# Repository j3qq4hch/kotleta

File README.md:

# kotleta
[3d view](https://a360.co/2SrLnso)

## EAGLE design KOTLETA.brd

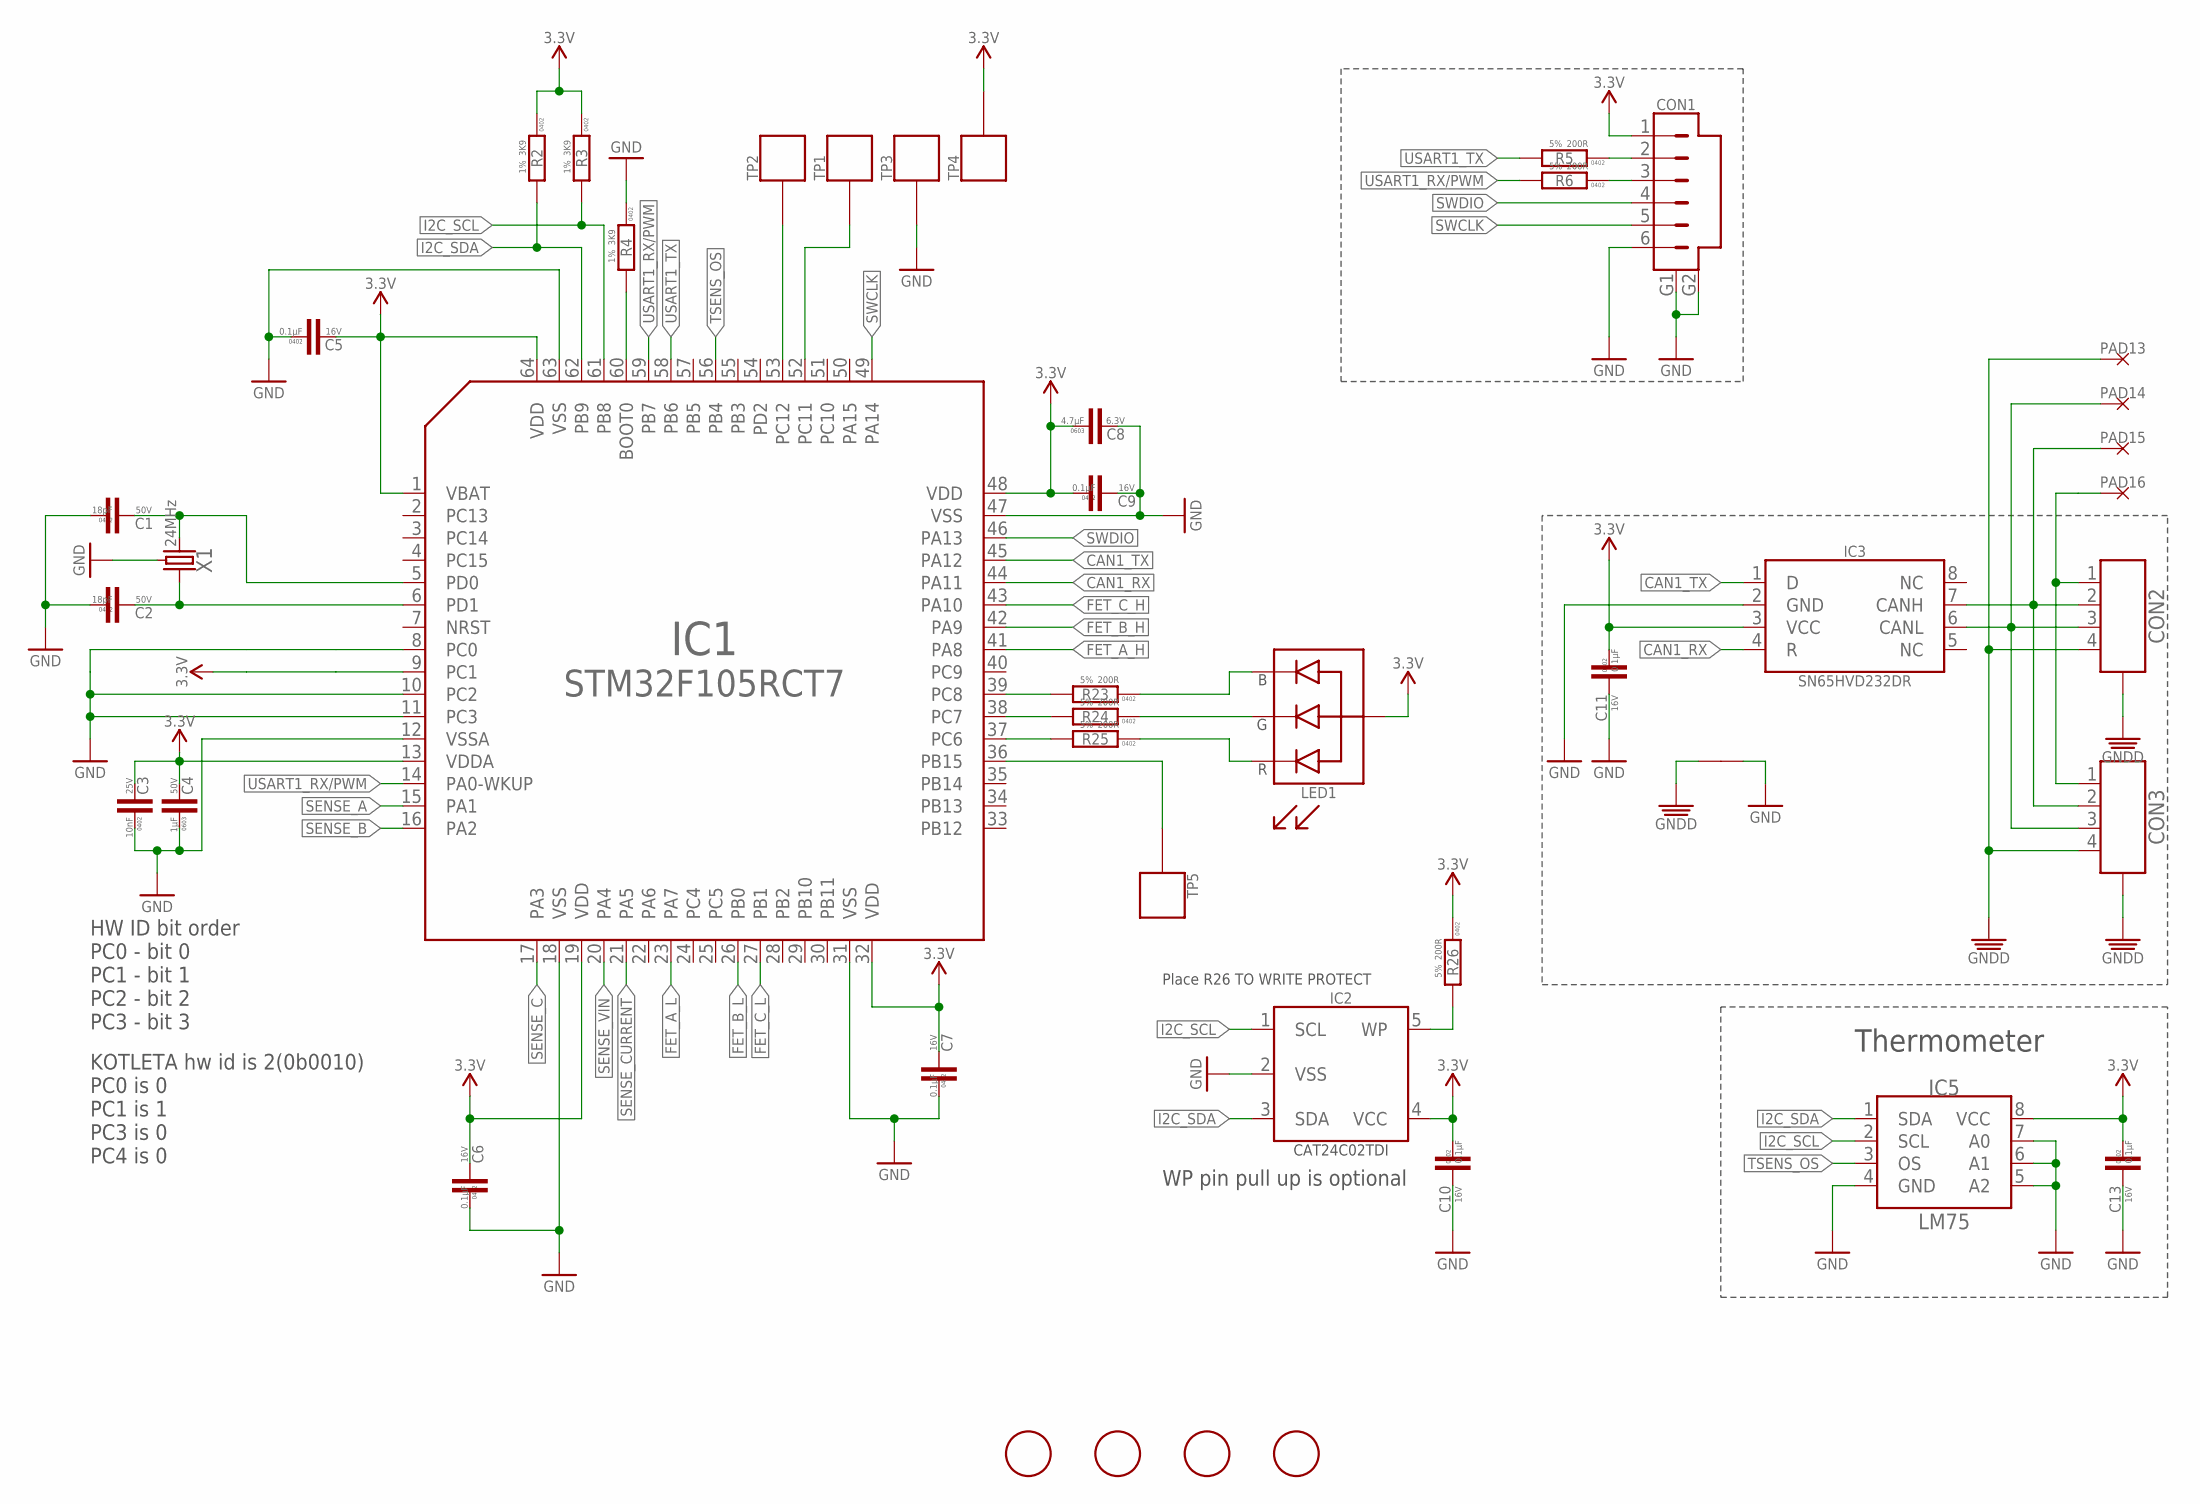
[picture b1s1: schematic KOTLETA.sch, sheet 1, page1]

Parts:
C1, C2: 18pF; C0402
C3: 10nF; C0402
C4: 1µF; C0603
C5, C6, C7, C9, C10, C11, C13: 0.1µF; C0402
C8: 4.7µF; C0603
CON1: CON-6P; SM06B; PARTNO SM06B-SRSS-TB
CON2, CON3: CON-4P-JST_GH-RA; JST_GH-4P-RA
FD1, FD2, FD3, FD4: FIDUCIALMOUNT; FIDUCIA-MOUNT
IC1: STM32F105RCT6; TQFP64; DIGIKEY# 497-11547-ND
IC2: CAT24C02; SOT23-5L
IC3: SN65HVD232D; SOIC8
IC5: LM75BD-TSSOP8; TSSOP8
LED1: LTST-C19HE1WT; LITE_ON_RGB_LED
PAD13, PAD14, PAD15, PAD16: PAD-HOLE-0.6; HOLE_0.6
R2, R3, R4: 3K9; R0402
R5, R6, R23, R24, R25, R26: 200R; R0402; PARTNO RC0402FR-07240RL
TP1, TP2, TP3, TP4, TP5: PAD.05; PAD.05X.05; PARTNO *
U$2: CONNECTION
X1: 24MHz; OSCILLATOR-3.2X2.5-4P; DIGIKEY# 1253-1198-1-ND

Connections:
BOOT0: IC1.60 (BOOT0), R4.2
CAN1_RX: IC1.44 (PA11), IC3.4 (R)
CAN1_TX: IC1.45 (PA12), IC3.1 (D)
FET_A_H: IC1.41 (PA8); also elsewhere on the board
FET_A_L: IC1.23 (PA7); also elsewhere on the board
FET_B_H: IC1.42 (PA9); also elsewhere on the board
FET_B_L: IC1.26 (PB0); also elsewhere on the board
FET_C_H: IC1.43 (PA10); also elsewhere on the board
FET_C_L: IC1.27 (PB1); also elsewhere on the board
GND: C1.1, C2.1, C3.1, C4.P$1 (1), C5.1, C6.1, C7.1, C8.P$2 (2), C9.2, C10.2, C11.2, C13.2, CON1.6, CON1.G1, CON1.G2, IC1.8 (PC0), IC1.10 (PC2), IC1.11 (PC3), IC1.12 (VSSA), IC1.18 (VSS), IC1.31 (VSS), IC1.47 (VSS), IC1.63 (VSS), IC2.2 (VSS), IC3.2 (GND), IC5.4 (GND), IC5.5 (A2), IC5.6 (A1), IC5.7 (A0), R4.1, TP3.P$1, U$2.P$2, X1.2 (GND), X1.4 (GND); also elsewhere on the board
GNDD: CON2.4, CON2.M$0 (GND), CON2.M$1 (GND), CON3.4, CON3.M$0 (GND), CON3.M$1 (GND), PAD13.P$1, U$2.P$1
I2C_SCL: IC1.61 (PB8), IC2.1 (SCL), IC5.2 (SCL), R3.2
I2C_SDA: IC1.62 (PB9), IC2.3 (SDA), IC5.1 (SDA), R2.2
unnamed: CON1.2, R5.1
unnamed: CON1.3, R6.1
unnamed: IC1.37 (PC6), R25.2
unnamed: LED1.B, R23.1
unnamed: LED1.R, R25.1
unnamed: IC2.5 (WP), R26.2
unnamed: IC1.38 (PC7), R24.2
unnamed: C1.2, IC1.5 (PD0), X1.3 (2)
unnamed: IC1.39 (PC8), R23.2
unnamed: C2.2, IC1.6 (PD1), X1.1
unnamed: CON2.1, CON3.1, PAD16.P$1
unnamed: CON2.2, CON3.2, IC3.7 (CANH), PAD15.P$1
unnamed: CON2.3, CON3.3, IC3.6 (CANL), PAD14.P$1
unnamed: LED1.G, R24.1
unnamed: IC1.53 (PC12), TP2.P$1
unnamed: IC1.36 (PB15), TP5.P$1
unnamed: IC1.52 (PC11), TP1.P$1
SENSE_A: IC1.15 (PA1); also elsewhere on the board
SENSE_B: IC1.16 (PA2); also elsewhere on the board
SENSE_C: IC1.17 (PA3); also elsewhere on the board
SENSE_CURRENT: IC1.21 (PA5); also elsewhere on the board
SENSE_VIN: IC1.20 (PA4); also elsewhere on the board
SWCLK: CON1.5, IC1.49 (PA14)
SWDIO: CON1.4, IC1.46 (PA13)
TSENS_OS: IC1.56 (PB4), IC5.3 (OS)
USART1_RX/PWM: IC1.14 (PA0-WKUP), IC1.59 (PB7), R6.2
USART1_TX: IC1.58 (PB6), R5.2
VDD_3V3: C3.2, C4.P$2 (2), C5.2, C6.2, C7.2, C8.P$1 (1), C9.1, C10.1, C11.1, C13.1, CON1.1, IC1.1 (VBAT), IC1.9 (PC1), IC1.13 (VDDA), IC1.19 (VDD), IC1.32 (VDD), IC1.48 (VDD), IC1.64 (VDD), IC2.4 (VCC), IC3.3 (VCC), IC5.8 (VCC), LED1.+ (A), R2.1, R3.1, R26.1, TP4.P$1; also elsewhere on the board

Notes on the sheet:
Thermometer
Place R26 TO WRITE PROTECT
WP pin pull up is optional
HW ID bit order PC0 - bit 0 PC1 - bit 1 PC2 - bit 2 PC3 - bit 3
KOTLETA hw id is 2(0b0010) PC0 is 0 PC1 is 1 PC3 is 0 PC4 is 0

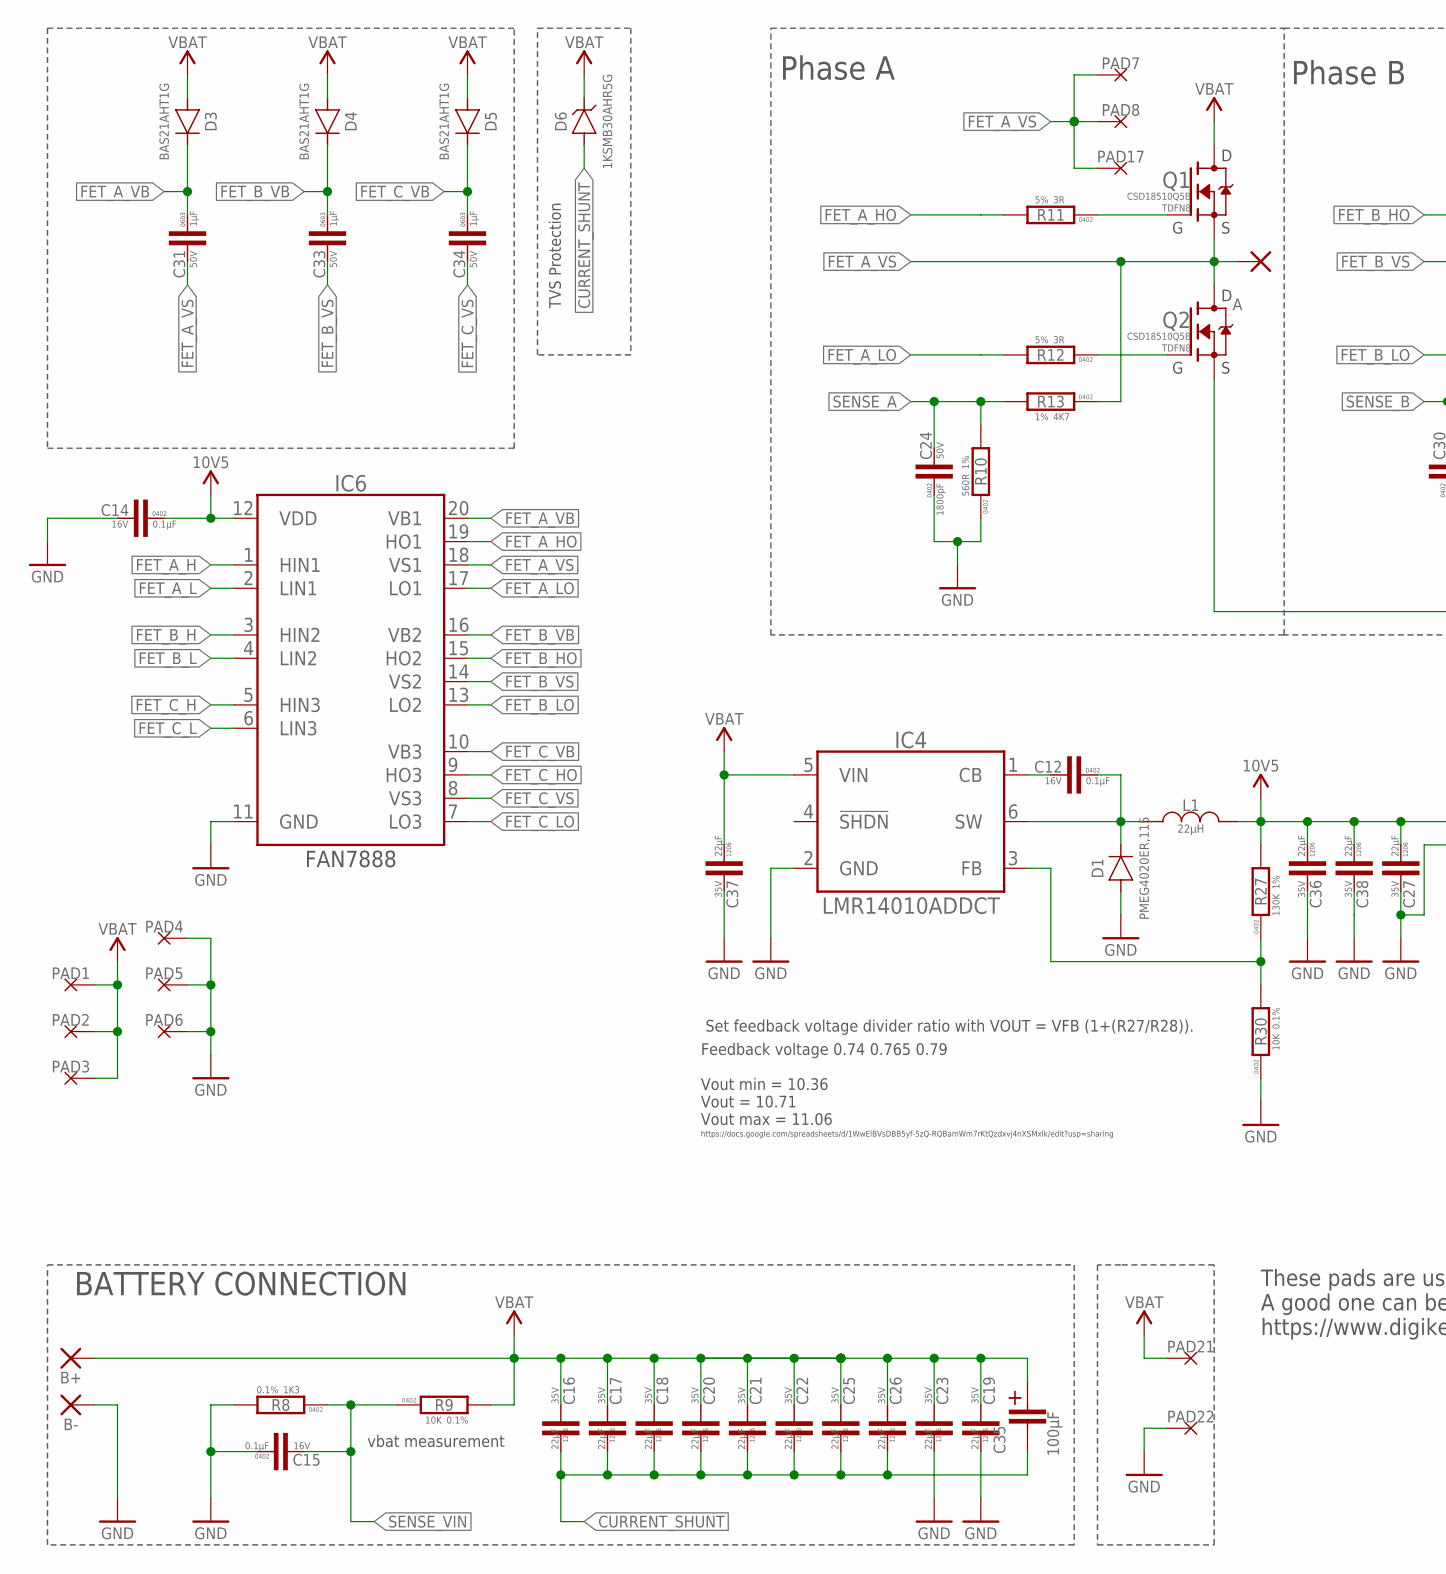
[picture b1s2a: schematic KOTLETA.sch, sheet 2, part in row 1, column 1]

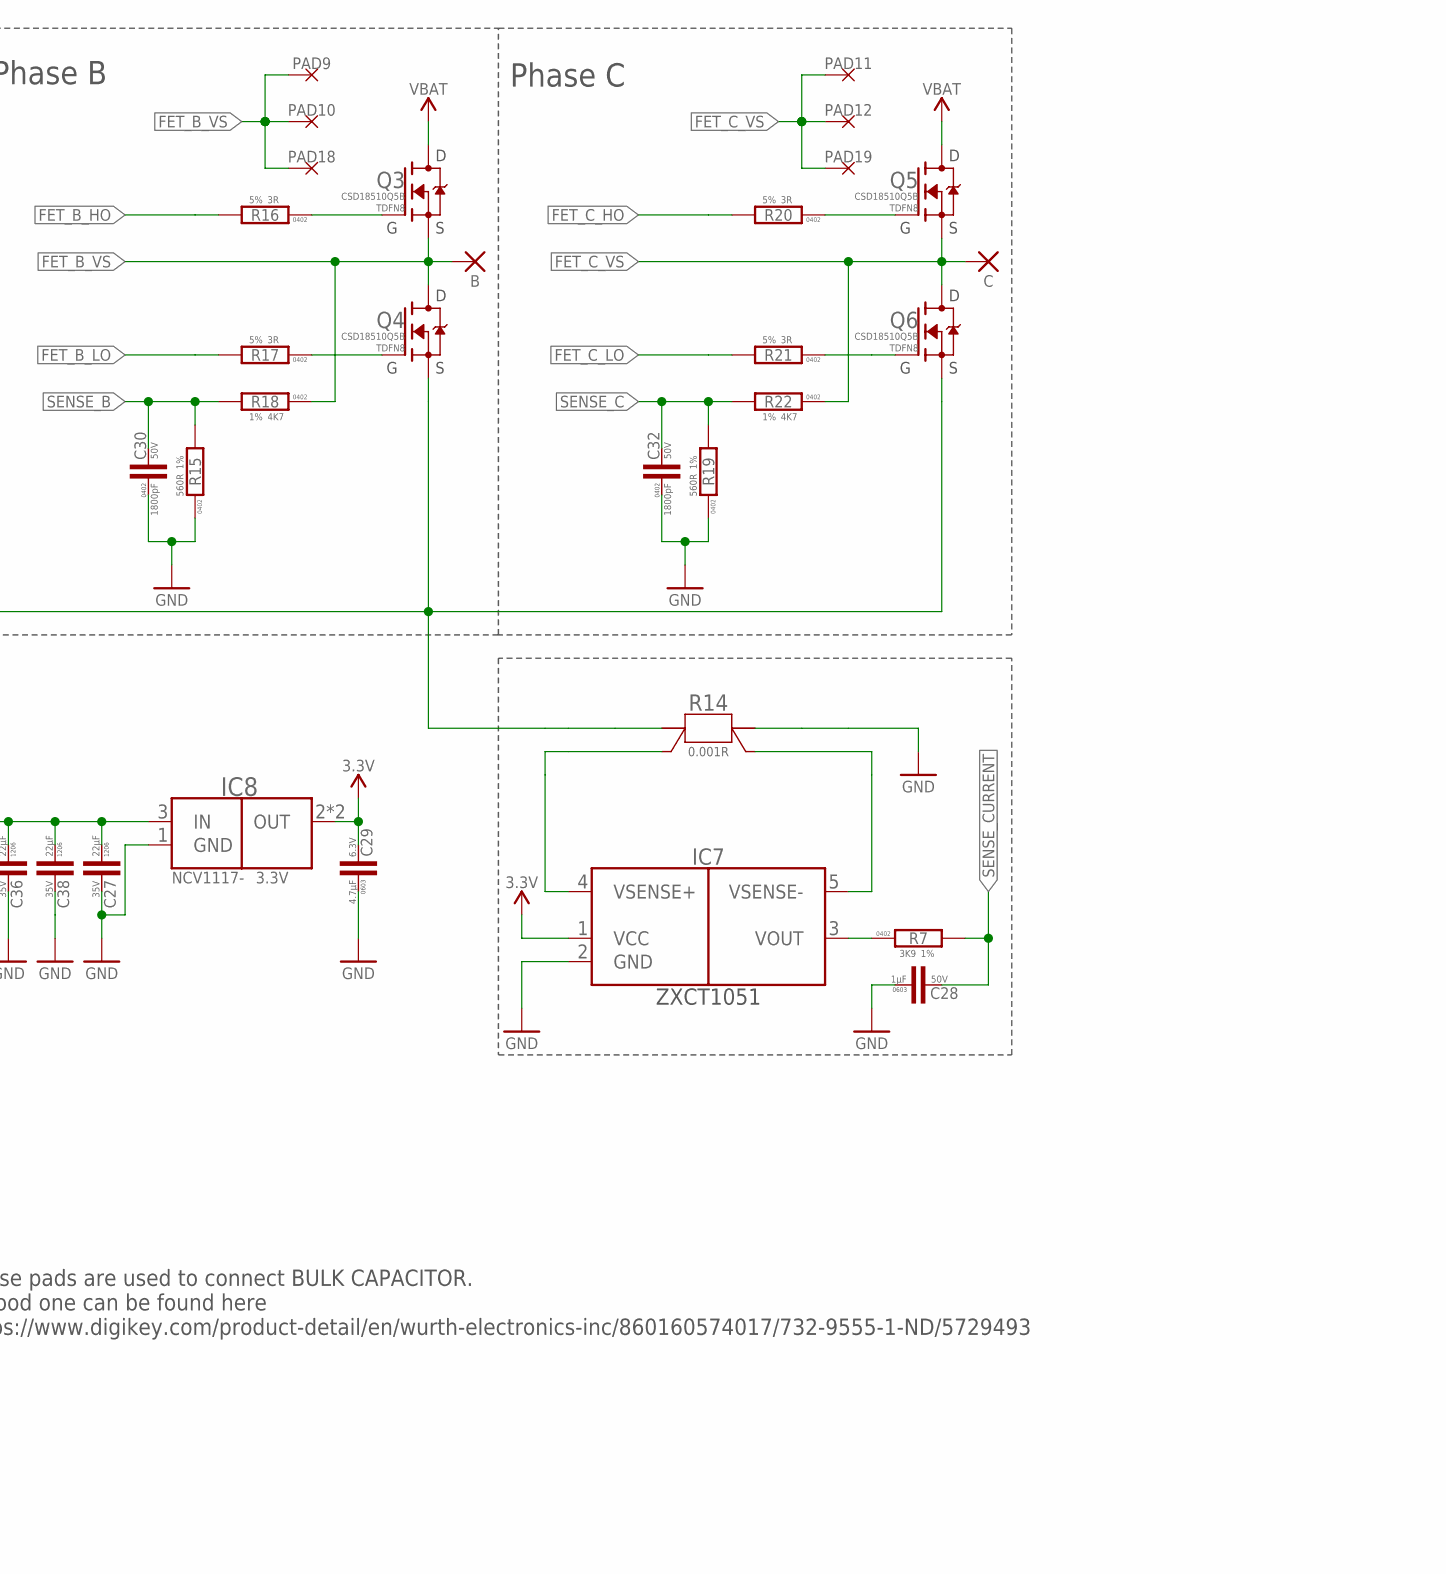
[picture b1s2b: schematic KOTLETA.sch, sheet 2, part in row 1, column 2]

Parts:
A: WIREPADSMD5-2,5; 5-2,5
B: WIREPADSMD5-2,5; 5-2,5
B+: WIREPADSMD5-2,5; 5-2,5
B-: WIREPADSMD5-2,5; 5-2,5
C: WIREPADSMD5-2,5; 5-2,5
C12, C14, C15: 0.1µF; C0402
C16, C17, C18, C19, C20, C21, C22, C23, C25, C26, C27, C36, C37, C38: 22µF; C1206
C24, C30, C32: 1800pF; C0402
C28, C31, C33, C34: 1µF; C0603
C29: 4.7µF; C0603
C35: 100µF; 3024
D1: PMEG4020; SOD123W
D3, D4, D5: BAS21AHT1G; SOD323
D6: 1KSMB30AHR5G; DO-214AA(SMB)
IC4: LMR14010ADDCT; SOT23-6
IC6: FAN7888; SOIC20; PARTNO FAN7888MX
IC7: ZXCT1051; SOT23-5L
IC8: 3.3V; SOT-223
L1: 22µH; SRN5040
PAD1, PAD2, PAD3, PAD4, PAD5, PAD6, PAD7, PAD8, PAD9, PAD10, PAD11, PAD12, PAD17, PAD18, PAD19: PAD-HOLE-0.6; HOLE_0.6
PAD21, PAD22: PAD-HOLE-0.8; HOLE_0.8
Q1, Q2, Q3, Q4, Q5, Q6: CSD18510Q5B; PG-TDSON-8
R7: 3K9; R0402
R8: 1K3; R0402
R9, R30: 10K; R0402
R10, R15, R19: 560R; R0402
R11, R12, R16, R17, R20, R21: 3R; R0402
R13, R18, R22: 4K7; R0402
R14: 0.001R; R2010-KELVIN
R27: 130K; R0402; DIGIKEY# YAG2969CT-ND

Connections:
BLABLA: IC7.3 (VOUT), R7.1
CURRENT_SHUNT: C16.P$1 (1), C17.P$1 (1), C18.P$1 (1), C20.P$1 (1), C21.P$1 (1), C22.P$1 (1), C25.P$1 (1), C26.P$1 (1), C35.-, D6.A, Q2.1S (S), Q2.2S (S), Q2.3S (S), Q4.1S (S), Q4.2S (S), Q4.3S (S), Q6.1S (S), Q6.2S (S), Q6.3S (S), R14.1, R14.11 (1)
FET_A_H: IC6.1 (HIN1); also elsewhere on the board
FET_A_HO: IC6.19 (HO1), R11.2
FET_A_L: IC6.2 (LIN1); also elsewhere on the board
FET_A_LO: IC6.17 (LO1), R12.2
FET_A_VB: C31.P$1 (1), D3.C, IC6.20 (VB1)
FET_A_VS: A.1, C31.P$2 (2), IC6.18 (VS1), PAD7.P$1, PAD8.P$1, PAD17.P$1, Q1.1S (S), Q1.2S (S), Q1.3S (S), Q2.5D (D), Q2.6D (D), Q2.7D (D), Q2.8D (D), Q2.PAD_D (D), R13.1
FET_B_H: IC6.3 (HIN2); also elsewhere on the board
FET_B_HO: IC6.15 (HO2), R16.2
FET_B_L: IC6.4 (LIN2); also elsewhere on the board
FET_B_LO: IC6.13 (LO2), R17.2
FET_B_VB: C33.P$1 (1), D4.C, IC6.16 (VB2)
FET_B_VS: B.1, C33.P$2 (2), IC6.14 (VS2), PAD9.P$1, PAD10.P$1, PAD18.P$1, Q3.1S (S), Q3.2S (S), Q3.3S (S), Q4.5D (D), Q4.6D (D), Q4.7D (D), Q4.8D (D), Q4.PAD_D (D), R18.1
FET_C_H: IC6.5 (HIN3); also elsewhere on the board
FET_C_HO: IC6.9 (HO3), R20.2
FET_C_L: IC6.6 (LIN3); also elsewhere on the board
FET_C_LO: IC6.7 (LO3), R21.2
FET_C_VB: C34.P$1 (1), D5.C, IC6.10 (VB3)
FET_C_VS: C.1, C34.P$2 (2), IC6.8 (VS3), PAD11.P$1, PAD12.P$1, PAD19.P$1, Q5.1S (S), Q5.2S (S), Q5.3S (S), Q6.5D (D), Q6.6D (D), Q6.7D (D), Q6.8D (D), Q6.PAD_D (D), R22.1
GND: B-.1, C14.2, C15.1, C19.P$1 (1), C23.P$1 (1), C24.1, C27.P$2 (2), C28.P$1 (1), C29.P$1 (1), C30.1, C32.1, C36.P$2 (2), C37.P$2 (2), C38.P$2 (2), D1.A, IC4.2 (GND), IC6.11 (GND), IC7.2 (GND), IC8.1 (GND), PAD4.P$1, PAD5.P$1, PAD6.P$1, PAD22.P$1, R8.2, R10.1, R14.2, R14.22 (2), R15.1, R19.1, R30.1; also elsewhere on the board
unnamed: Q2.4G (G), R12.1
unnamed: Q3.4G (G), R16.1
unnamed: Q4.4G (G), R17.1
unnamed: Q5.4G (G), R20.1
unnamed: IC7.5 (VSENSE-), R14.S2
unnamed: Q1.4G (G), R11.1
unnamed: Q6.4G (G), R21.1
unnamed: C12.1, D1.C, IC4.6 (SW), L1.P$1
unnamed: IC7.4 (VSENSE+), R14.S1
unnamed: IC4.3 (FB), R27.1, R30.2
unnamed: C12.2, IC4.1 (CB)
SENSE_A: C24.2, R10.2, R13.2; also elsewhere on the board
SENSE_B: C30.2, R15.2, R18.2; also elsewhere on the board
SENSE_C: C32.2, R19.2, R22.2; also elsewhere on the board
SENSE_CURRENT: C28.P$2 (2), R7.2; also elsewhere on the board
SENSE_VIN: C15.2, R8.1, R9.1; also elsewhere on the board
VBAT: B+.1, C16.P$2 (2), C17.P$2 (2), C18.P$2 (2), C19.P$2 (2), C20.P$2 (2), C21.P$2 (2), C22.P$2 (2), C23.P$2 (2), C25.P$2 (2), C26.P$2 (2), C35.+, C37.P$1 (1), D3.A, D4.A, D5.A, D6.C, IC4.5 (VIN), PAD1.P$1, PAD2.P$1, PAD3.P$1, PAD21.P$1, Q1.5D (D), Q1.6D (D), Q1.7D (D), Q1.8D (D), Q1.PAD_D (D), Q3.5D (D), Q3.6D (D), Q3.7D (D), Q3.8D (D), Q3.PAD_D (D), Q5.5D (D), Q5.6D (D), Q5.7D (D), Q5.8D (D), Q5.PAD_D (D), R9.2
VDD_3V3: C29.P$2 (2), IC7.1 (VCC), IC8.2 (OUT), IC8.4 (OUT); also elsewhere on the board
VDD_10V5: C14.1, C27.P$1 (1), C36.P$1 (1), C38.P$1 (1), IC6.12 (VDD), IC8.3 (IN), L1.P$2, R27.2

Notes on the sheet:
vbat measurement
BATTERY CONNECTION
Phase A
Phase B
Phase C
TVS Protection
Set feedback voltage divider ratio with VOUT = VFB (1+(R27/R28)).
Feedback voltage 0.74 0.765 0.79
Vout min = 10.36 Vout = 10.71 Vout max = 11.06
https://docs.google.com/spreadsheets/d/1WwElBVsDBB5yf-5zQ-RQBamWm7rKtQzdxvj4nXSMxlk/edit?usp=sharing
These pads are used to connect BULK CAPACITOR. A good one can be found here https://www.digikey.com/product-detail/en/wurth-electronics-inc/860160574017/732-9555-1-ND/5729493

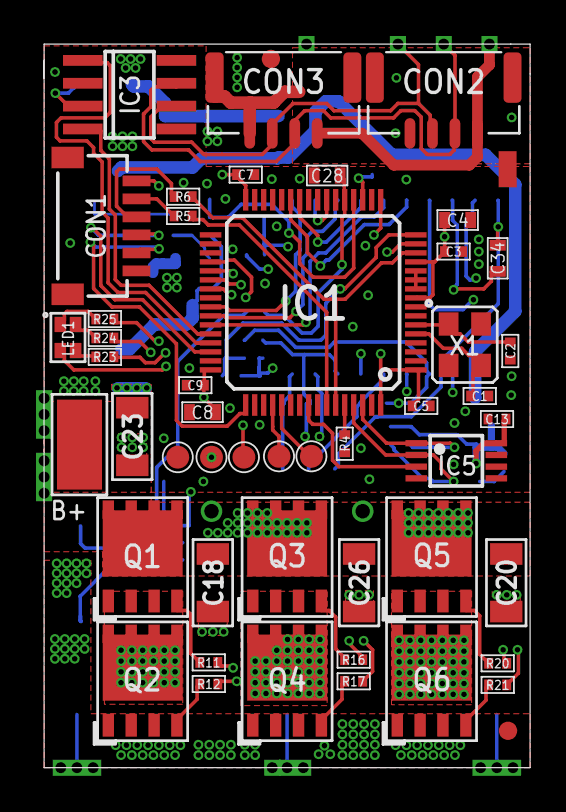
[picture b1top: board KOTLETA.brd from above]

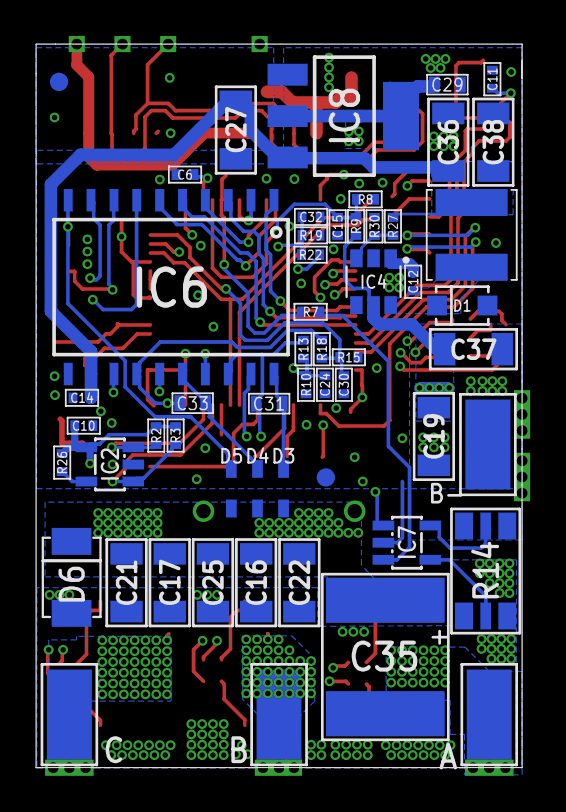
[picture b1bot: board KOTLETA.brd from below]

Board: 4 copper layers, 27.0 x 40.2 mm, 126 parts (64 on the bottom side), 68 nets.

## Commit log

2019-02-03 initial import
2019-02-03 proper gitignore
2019-02-03 routing done
2019-02-03 BETTER polygons
2019-02-03 minor fixes
2019-02-03 BOM fixes
2019-02-03 comments
2019-02-03 proper assembly variant
2019-02-03 BOM updates
2019-02-03 Its 10V5 noew. HW ID stuff also fixed
2019-02-03 pads for bulk capacitor
2019-02-03 blah
2019-02-03 notes
2019-02-04 minor updates
2019-02-04 DRC updates
